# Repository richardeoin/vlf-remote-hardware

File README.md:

EAGLE CAD Design files for the VLF Remote Unit

## Photo

## Design Notes

The board is based around a NXP
[LPC1114](http://www.nxp.com/documents/data_sheet/LPC111X.pdf) ARM
Cortex-M0 microcontroller. A Wolfson
[WM8737 ADC](http://www.wolfsonmicro.com/documents/uploads/data_sheets/en/WM8737.pdf)
is used to record the Very Low Frequency (VLF) signals. Although this
ADC is intended for audio applications it is perfectly adequate for
very low frequency RF signals due to its high gain preamplifiers. It
features low power operation and easily available, probably due to it
being
[used in the Microsoft Kinect](http://techon.nikkeibp.co.jp/english/NEWS_EN/20101205/187927/).

The board has three pads for serial flash and a
[AT86RF212](http://www.atmel.com/images/doc8168.pdf) 868MHz radio. The
range is in the order of 200m in free space, but much lower in practice.

The average current draw is approximately 3mA.

## [License](LICENSE.md)

[MIT](http://opensource.org/licenses/MIT)

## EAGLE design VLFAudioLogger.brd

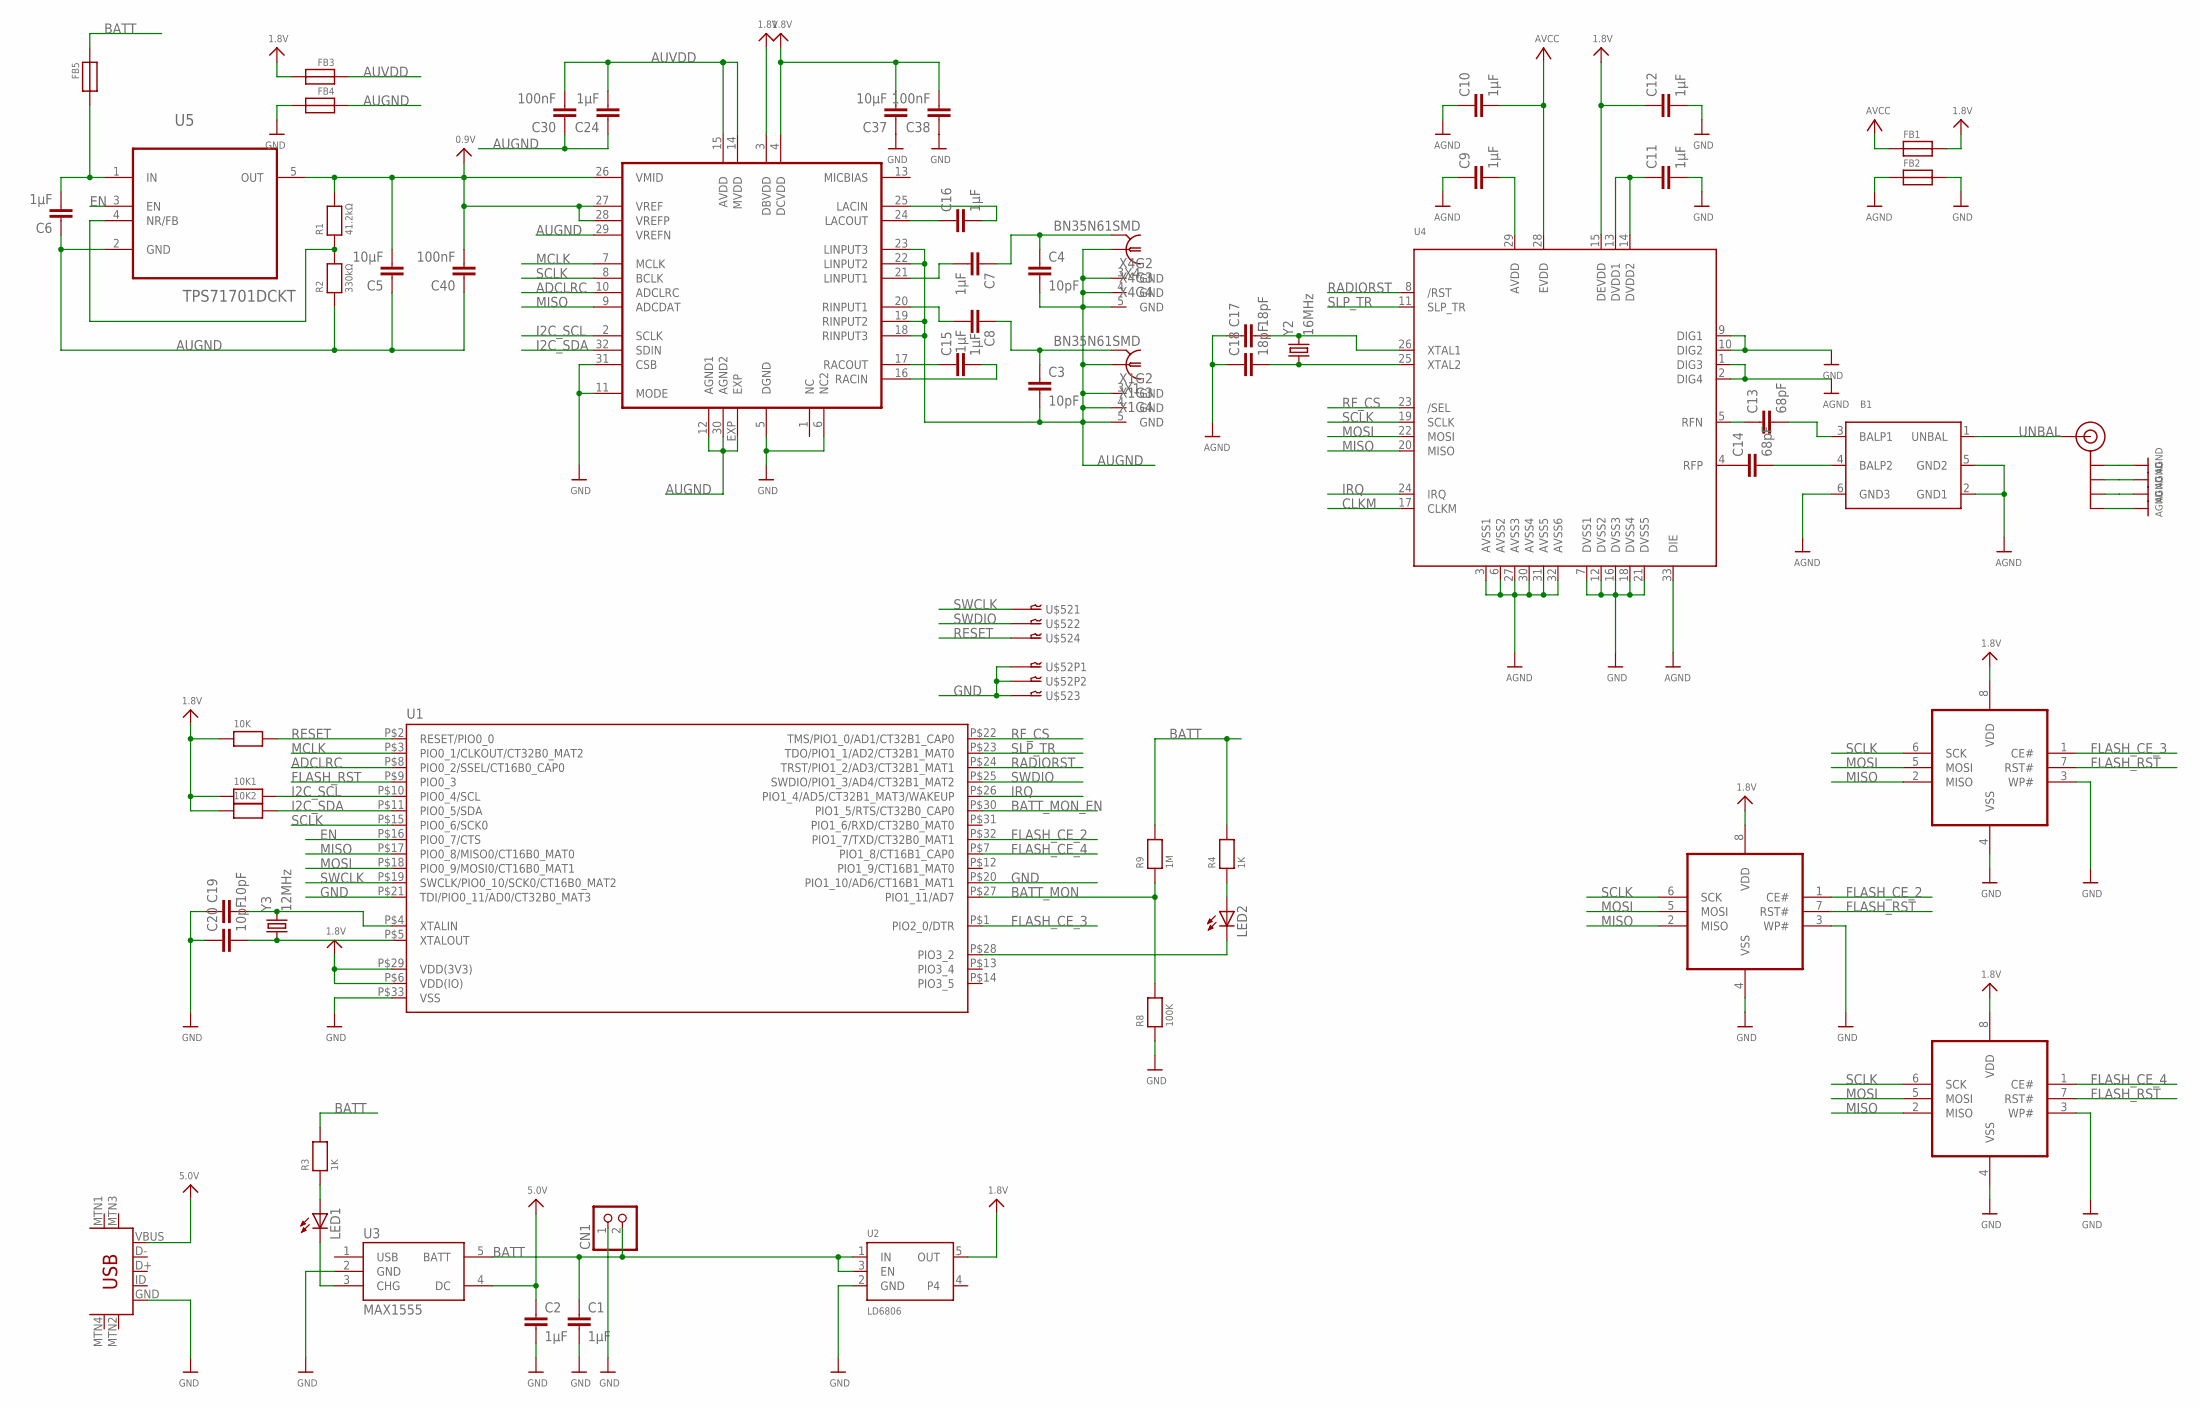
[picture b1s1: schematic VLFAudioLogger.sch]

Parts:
10K, 10K1, 10K2: RESISTOR0603MINI; 0603-MINI
B1: BALUN+LP; BALUN0805
C1, C2, C6, C7, C8, C9, C10, C11, C12, C15, C16, C24: 1µF; C0603K
C3, C4, C19, C20: 10pF; C0603K
C5, C37: 10µF; C0603K
C13, C14: 68pF; C0603K
C17, C18: 18pF; C0603K
C30, C38, C40: 100nF; C0603K
CN1: JST_2PIN; JSTPH2
FB1, FB2, FB3, FB4, FB5: FERRITE; 0603
J$1: SMA_EDGE; SMA-EDGE
LED1, LED2: LEDCHIPLED_0603; CHIPLED_0603
R1: 41.2kΩ; 0603-MINI
R2: 330kΩ; 0603-MINI
R3, R4: 1K; 0603-MINI
R8: 100K; 0603-MINI
R9: 1M; 0603-MINI
U1: LPC1113/4_QFN; HVQFN33-7X7
U2: LD6806; SOT23-5
U3: MAX1555; SOT23-5
U4: AT86RF212; 32QN2
U5: TPS71701DCKT; SOT65P210X110-5N
U$1, U$22, U$26: SST25WF; ZA
U$14: WM8737; DM030FL
U$16: USB-MINIB-5PIN; USB-MINIB
U$52: SM04B-SURS-TF
X1, X4: BN35N61SMD; B35N61_SMD
Y2: 16MHz; CRYSTAL-SMD-5X3
Y3: 12MHz; CRYSTAL-SMD-5X3

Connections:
0.9V: C5.2, C40.2, R1.2, U5.5 (OUT), U$14.26 (VMID), U$14.27 (VREF), U$14.28 (VREFP)
1.8V: 10K.1, 10K1.1, 10K2.1, C12.1, C37.2, C38.2, FB1.2, FB3.2, U1.P$6 (VDD(IO)), U1.P$29 (VDD(3V3)), U2.5 (OUT), U4.15 (DEVDD), U$1.8 (VDD), U$14.3 (DBVDD), U$14.4 (DCVDD), U$22.8 (VDD), U$26.8 (VDD)
5.0V: C2.1, U3.4 (DC), U$16.VBUS
ADCLRC: U1.P$8 (PIO0_2/SSEL/CT16B0_CAP0), U$14.10 (ADCLRC)
AGND: B1.2 (GND1), B1.5 (GND2), B1.6 (GND3), C9.1, C10.1, C17.1, C18.1, FB2.1, J$1.GND@0 (GND), J$1.GND@1 (GND), J$1.GND@2 (GND), J$1.GND@3 (GND), U4.1 (DIG3), U4.2 (DIG4), U4.3 (AVSS1), U4.6 (AVSS2), U4.27 (AVSS3), U4.30 (AVSS4), U4.31 (AVSS5), U4.32 (AVSS6), U4.33 (DIE)
AUBATT: C6.2, FB5.2, U5.1 (IN)
AUGND: C3.2, C4.2, C5.1, C6.1, C24.1, C30.1, C40.1, FB4.1, R2.1, U5.2 (GND), U$14.12 (AGND1), U$14.18 (RINPUT3), U$14.19 (RINPUT2), U$14.22 (LINPUT2), U$14.23 (LINPUT3), U$14.29 (VREFN), U$14.30 (AGND2), U$14.EXP, X1.2 (1), X1.3 (GND), X1.4 (GND), X1.5 (GND), X4.2 (1), X4.3 (GND), X4.4 (GND), X4.5 (GND)
AUVDD: C24.2, C30.2, FB3.1, U$14.14 (MVDD), U$14.15 (AVDD)
AVCC: C10.2, FB1.1, U4.28 (EVDD)
AVDD-IN: C9.2, U4.29 (AVDD)
BALP1: B1.3 (BALP1), C13.2
BALP2: B1.4 (BALP2), C14.2
BATT: C1.1, CN1.2, FB5.1, R3.2, R4.2, R9.2, U2.1 (IN), U2.3 (EN), U3.5 (BATT)
BATT_MON: R8.2, R9.1, U1.P$27 (PIO1_11/AD7)
BATT_MON_EN: U1.P$30 (PIO1_5/RTS/CT32B0_CAP0)
CHG: LED1.C, U3.3 (CHG)
CHG_LED: LED1.A, R3.1
CHG_LED1: LED2.A, R4.1
CLKM: U4.17 (CLKM)
EN: U1.P$16 (PIO0_7/CTS), U5.3 (EN)
FLASH_CE_2: U1.P$32 (PIO1_7/TXD/CT32B0_MAT1), U$26.1 (CE#)
FLASH_CE_3: U1.P$1 (PIO2_0/DTR), U$22.1 (CE#)
FLASH_CE_4: U1.P$7 (PIO1_8/CT16B1_CAP0), U$1.1 (CE#)
FLASH_RST: U1.P$9 (PIO0_3), U$1.7 (RST#), U$22.7 (RST#), U$26.7 (RST#)
GND: C1.2, C2.2, C11.2, C12.2, C19.1, C20.1, C37.1, C38.1, CN1.1, FB2.2, FB4.2, R8.1, U1.P$20 (PIO1_10/AD6/CT16B1_MAT1), U1.P$21 (TDI/PIO0_11/AD0/CT32B0_MAT3), U1.P$33 (VSS), U2.2 (GND), U3.2 (GND), U4.7 (DVSS1), U4.9 (DIG1), U4.10 (DIG2), U4.12 (DVSS2), U4.16 (DVSS3), U4.18 (DVSS4), U4.21 (DVSS5), U$1.3 (WP#), U$1.4 (VSS), U$14.5 (DGND), U$14.6 (NC2), U$14.11 (MODE), U$14.31 (CSB), U$16.GND, U$22.3 (WP#), U$22.4 (VSS), U$26.3 (WP#), U$26.4 (VSS), U$52.3, U$52.GND1, U$52.GND2
I2C_SCL: 10K1.2, U1.P$10 (PIO0_4/SCL), U$14.2 (SCLK)
I2C_SDA: 10K2.2, U1.P$11 (PIO0_5/SDA), U$14.32 (SDIN)
IRQ: U1.P$26 (PIO1_4/AD5/CT32B1_MAT3/WAKEUP), U4.24 (IRQ)
LPC_XTAL1: C19.2, U1.P$4 (XTALIN), Y3.3 (2)
LPC_XTAL2: C20.2, U1.P$5 (XTALOUT), Y3.1
MCLK: U1.P$3 (PIO0_1/CLKOUT/CT32B0_MAT2), U$14.7 (MCLK)
MISO: U1.P$17 (PIO0_8/MISO0/CT16B0_MAT0), U4.20 (MISO), U$1.2 (MISO), U$14.9 (ADCDAT), U$22.2 (MISO), U$26.2 (MISO)
MOSI: U1.P$18 (PIO0_9/MOSI0/CT16B0_MAT1), U4.22 (MOSI), U$1.5 (MOSI), U$22.5 (MOSI), U$26.5 (MOSI)
unnamed: LED2.C, U1.P$28 (PIO3_2)
unnamed: C8.2, U$14.20 (RINPUT1)
unnamed: C3.1, C8.1, X1.1 (GND)
unnamed: C4.1, C7.1, X4.1 (GND)
unnamed: C11.1, U4.13 (DVDD1), U4.14 (DVDD2)
unnamed: C7.2, U$14.21 (LINPUT1)
unnamed: C16.1, U$14.24 (LACOUT)
unnamed: C15.1, U$14.17 (RACOUT)
unnamed: C16.2, U$14.25 (LACIN)
unnamed: C15.2, U$14.16 (RACIN)
unnamed: R1.1, R2.2, U5.4 (NR/FB)
RADIORST: U1.P$24 (TRST/PIO1_2/AD3/CT32B1_MAT1), U4.8 (/RST)
RESET: 10K.2, U1.P$2 (RESET/PIO0_0), U$52.4
RFN: C13.1, U4.5 (RFN)
RFP: C14.1, U4.4 (RFP)
RF_CS: U1.P$22 (TMS/PIO1_0/AD1/CT32B1_CAP0), U4.23 (/SEL)
RF_XTAL1: C17.2, U4.26 (XTAL1), Y2.3 (2)
RF_XTAL2: C18.2, U4.25 (XTAL2), Y2.1
SCLK: U1.P$15 (PIO0_6/SCK0), U4.19 (SCLK), U$1.6 (SCK), U$14.8 (BCLK), U$22.6 (SCK), U$26.6 (SCK)
SLP_TR: U1.P$23 (TDO/PIO1_1/AD2/CT32B1_MAT0), U4.11 (SLP_TR)
SWCLK: U1.P$19 (SWCLK/PIO0_10/SCK0/CT16B0_MAT2), U$52.1
SWDIO: U1.P$25 (SWDIO/PIO1_3/AD4/CT32B1_MAT2), U$52.2
UNBAL: B1.1 (UNBAL), J$1.SIG (SIGNAL)

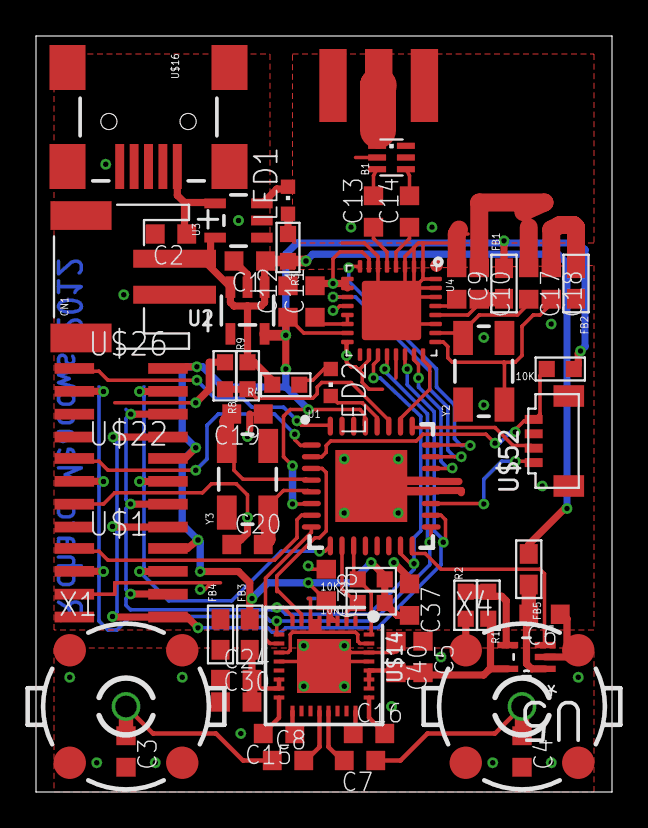
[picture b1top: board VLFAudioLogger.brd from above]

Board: 2 copper layers, 32.0 x 42.0 mm, 59 parts (0 on the bottom side), 54 nets.

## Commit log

2013-10-28 Version 1
2013-10-28 Version 2
2013-10-28 Version 3
2013-10-28 Version 4
2013-10-28 Added photo, renamed EAGLE Design Files
2013-10-28 Added basic LICENSE and README
2013-10-28 Wrote Design Notes
2013-10-28 Made photo link work
2013-10-29 Spelling fix
